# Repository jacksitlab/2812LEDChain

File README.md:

## 2812LEDChain

This Project is based on a little piece of Hardware I build for accessing 2812LEDs via I2C-Bus(aka TWI). In my special case I use a Raspberry PI to control them.
The Clou: It is possible to wire them from board to board and control them seperately. So you can wire the seperated LEDChains from one to another.
The Controller works like a simple 32bit adressable I2C-EEPROM where you can write the RGB-Values.

## Why the extra board? There is already a lib for the raspi that can control 2812LEDs.

Yeah, thats right. But this lib is using the PWM-output Pin and many of my Projects are using this as it should be. That's why I want to put it on a place where I can control them with a seperate address.
 
## Folders

* pcb: all KiCAD files (Schematics and Layout files)
* firmware: all microcontroller files for CodeComposerStudio(from Texas Instruments)
* raspberry: all files to remote control the LEDChain from a Raspberry PI with python

## Installation / Usage

### Firmware installation

* File > Import > Code Composer Studio > CCS Projects
* Select Directory and Finish
* Debug with a programmer (a launchpad also works) with connected TEST and RESET Pin. Don't forget GND.

### For Raspberry PI with Python

* copy ws2812ledchain.py to your python project folder
* use it from a seperate file like this below.

```
	
	from ws2812ledchain import *

	chain=WS2812Chain(1)  //1 =>bus number(i2c-1 on raspi 2 and 3, i2c-0 on raspi 1)
	leds=chain.Add(0x44,256)  //0x44 => 7bit address of the chain element. 0x44 is the default. can be modified in firmware, 256 leds to handle
	leds.Test()
	leds.RingBuffer(500,0)  //shift forward every LED every 500ms 
	time.sleep(5)
	leds.RingBuffer(100,1)  //shift backward every LED every 100ms

```

### For Raspberry PI with Web-API

* install apache webserver

```

	pi@raspberrypi ~ $ sudo apt-get install apache2

```

* copy ws2812ledchain.py and api.py to /usr/lib/cgi-bin/
* change userrights for those files

```

	pi@raspberrypi ~ $ sudo chmod 0755 /usr/lib/cgi-bin/*.py

```

* add cgi support in your apache config file

```

	<Directory "/usr/lib/cgi-bin">
		AllowOverride None
		Options +ExecCGI -MultiViews +SymLinksIfOwnerMatch
		Order allow,deny
		Allow from all
	</Directory>

```

* maybe you have to enable cgi mod for apache

```

	sudo a2enmod cgi
	sudo /etc/init.d/apache2 restart
```

* make a simple get request with javascript from your page (here with jQuery)

```

	$.ajax({
		url:'cgi-bin/api.py?task='+task,
		success: function(r){
			console.log(r);
		}
    });

```

## TODO

* Set RGBChain Length via Command
* Change I2C-Address via Command
* Add more functions ...

## License

Beerware License.

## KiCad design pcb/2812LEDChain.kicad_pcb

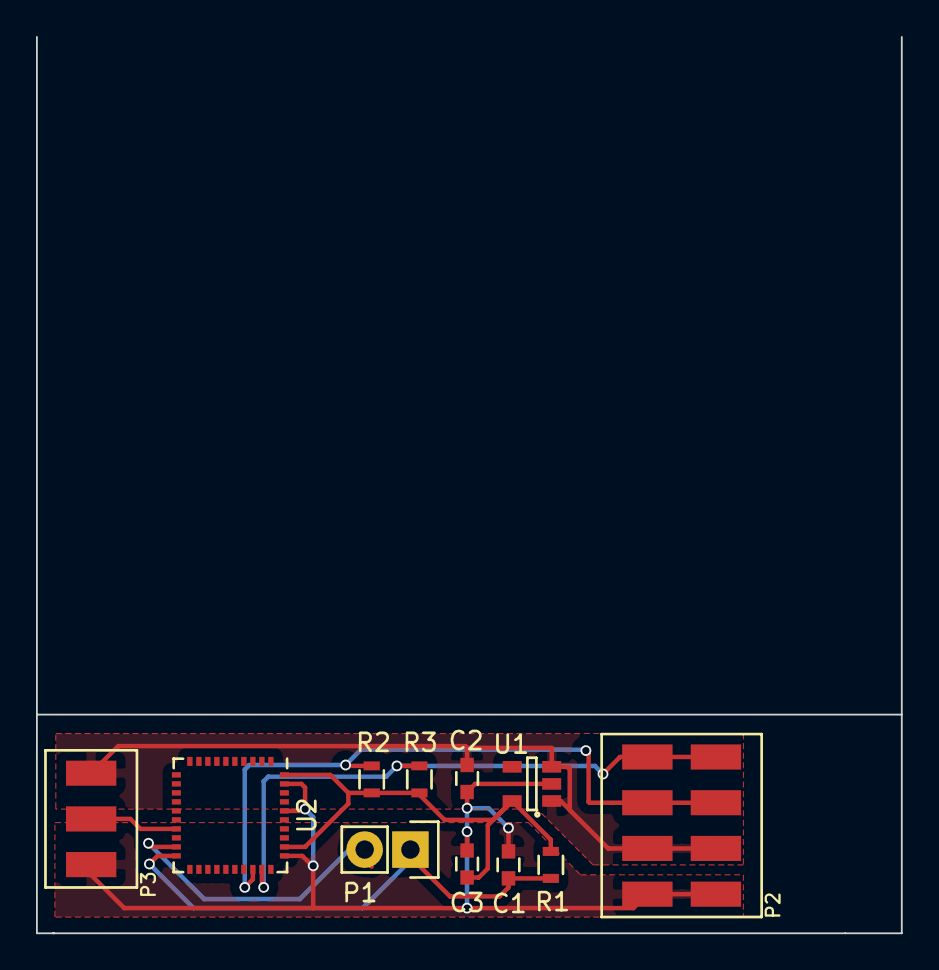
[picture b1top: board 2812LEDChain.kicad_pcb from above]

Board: 2 copper layers, 48.1 x 49.8 mm, 11 parts (0 on the bottom side), 8 nets.

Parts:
C1: 1n; C_0603
C2, C3: 1u; C_0603
P1: CONN_01X02; Pin_Header_Straight_1x02
P2: CONN_02X04; PINHEAD1-8_SMD
P3: CONN_01X03; PINHEAD1-3_SMD
R1: 47k; R_0603
R2, R3: 10k; R_0603
U1: LD59015; SOT-23-5
U2: MSP430F5739; QFN-40-1EP_6x6mm_Pitch0.5mm

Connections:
+3V3: C3.1, R1.1, R2.1, R3.1, U1.5, U2.32, U2.40
+5V: C2.1, P2.5, P2.6, P3.1, U1.1, U1.3
/DO: P3.2, U2.17
/RST: C1.1, P1.1, R1.2, U2.20
/SCL: P2.1, P2.2, R3.2, U2.29
/SDA: P2.3, P2.4, R2.2, U2.28
/TEST: P1.2, U2.19
GND: C1.2, C2.2, C3.2, P2.7, P2.8, P3.3, U1.2, U2.31, U2.36, U2.39

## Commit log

2016-08-21 :confetti_ball: Added .gitattributes
2016-10-26 some small changes
2016-10-29 added fadein and fadeout
2016-10-29 add fadein and out ltr
2018-06-17 fixed dstmembug, works with 256 leds
2018-06-17 fixed readme
